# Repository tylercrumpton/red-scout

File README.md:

# Red Scout
## Multi-Purpose Wireless Sensor and Controller Board
Red Scout is a wireless module designed to allow easy collection of data from a variety of sensors, as well providing the ability to control devices like LEDs, relays, motors, and more. It's based on the Synapse SM200 SNAP module, a microcontroller with built-in 802.15.4 wireless meshing that runs Python scripts.

### Overall Features
- Simple wireless communication
- Runs SNAPpy Python scripts
- Open Hardware (CC-BY-SA 4.0)
- Board is customizable for many purposes at assembly time
- Small (less than 10x10cm)
- Uses snap fasteners for connecting sensors and devices

### Assembly-time Configuration
To configure the IO pads of the Red Scout at assembly time, a resistor or jumper can be added to the PD or PU resistor pads for that IO. A resistor soldered to the PD pads is placed between the IO pad and GND, whereas a resistor soldered to the PU pads is placed between the IO pad and VCC. By soldering a zero ohm resistor on PD or PU, the IO pad can be used as VCC or GND instead of its IO function. Example hardware configurations will be added to the documentation in the future.

### AA-Version Features

- Powered by two AA batteries
  - Can last up to year in low power mode
- Two LEDs controlled by PWM pins
- 8 GPIO
  - Each GPIO can be configured to have a pullup or pulldown
  - SPI pins (MISO, MOSI, CLK)
  - I2C pins (SCL, SDA, CLK)
  - UART pins (TX, RX)
  - PWM pin
  - 4 analog inputs
- 3mm mounting holes

### Pinouts

To simplify programming, pin equivalence is given in the table below.

| SM200 pin | Pin Name | RedScout | SNAPpy IO |
|-----------|----------|----------|-----------|
| D3        | PWM7     | P1       |         7 |
| B7        | SCL      | P2       |        31 |
| A7        | SDA      | P3       |        30 |
| B4        | MOSI     | P4       |        25 |
| B1        | MISO     | P5       |        18 |
| A5        | CLK      | P6       |        26 |
| C2        | TX0      | P7       |        17 |
| C1        | RX0      | P8       |        16 |
| D2        | PWM6     | D2       |         6 |
| D1        | PWM5     | D1       |         5 |

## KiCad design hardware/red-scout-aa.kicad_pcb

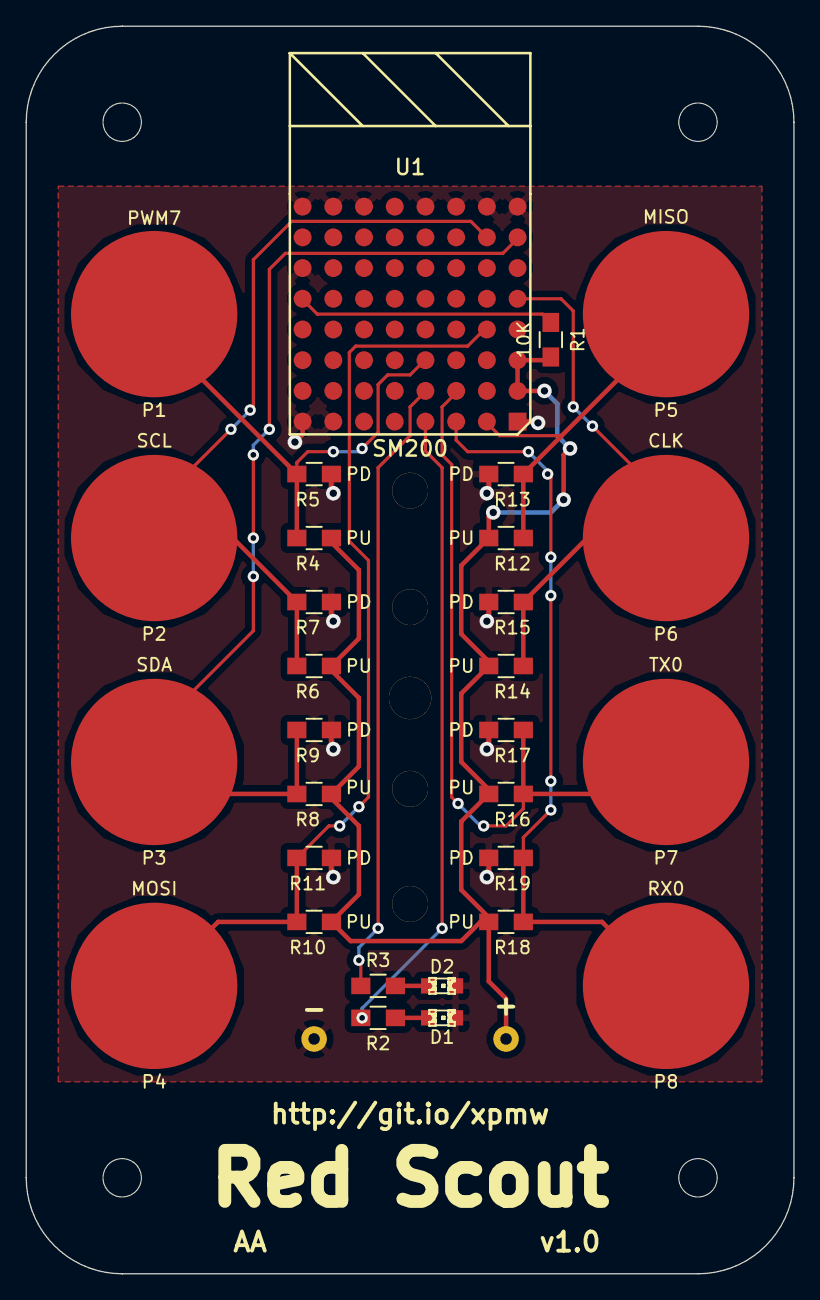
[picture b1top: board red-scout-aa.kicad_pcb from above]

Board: 2 copper layers, 60.0 x 97.5 mm, 35 parts (1 on the bottom side), 15 nets.

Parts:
BT1: BATTERY; AA_battery_holder_12BH321P-GR
D1, D2: LED; LED-0805
MountingHole_3mm, MountingHole_3mm#2, MountingHole_3mm#3, MountingHole_3mm#4: VAL**; MountingHole_3mm
P1: PWM7; 16_snap
P2: SCL; 16_snap
P3: SDA; 16_snap
P4: MOSI; 16_snap
P5: MISO; 16_snap
P6: CLK; 16_snap
P7: TX0; 16_snap
P8: RX0; 16_snap
R1: 10K; R_0805_HandSoldering
R2, R3: 1K; R_0805_HandSoldering
R4, R6, R8, R10, R12, R14, R16, R18: PU; R_0805_HandSoldering
R5, R7, R9, R11, R13, R15, R17, R19: PD; R_0805_HandSoldering
U1: SM200

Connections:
GND: BT1.2, D1.2, D2.2, R5.2, R7.2, R9.2, R11.2, R13.2, R15.2, R17.2, R19.2, U1.A1, U1.A8, U1.B8, U1.C8, U1.D8, U1.F8, U1.G1, U1.G8, U1.H1, U1.H6, U1.H8
MISO: P5.1, R12.1, R13.1, U1.B1
MOSI: P4.1, R10.1, R11.1, U1.B4
unnamed: D1.1, R2.2
unnamed: D2.1, R3.2
unnamed: R1.1, U1.H5
PWM5: R2.1, U1.D1
PWM6: R3.1, U1.D2
PWM7: P1.1, R4.1, R5.1, U1.D3
RX0: P8.1, R18.1, R19.1, U1.C1
SCL: P2.1, R6.1, R7.1, U1.B7
SDA: P3.1, R8.1, R9.1, U1.A7
SPICLK: P6.1, R14.1, R15.1, U1.A5
TX0: P7.1, R16.1, R17.1, U1.C2
VCC: BT1.1, R1.2, R4.2, R6.2, R8.2, R10.2, R12.2, R14.2, R16.2, R18.2, U1.A2, U1.A3

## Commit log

2015-03-05 Started schematic for AA-powered red-scout board.
2015-03-05 Added snap connectors and LEDs.
2015-03-05 Wired up the snaps and nc'ed the unused pins.
2015-03-05 Placed all parts on PCB.
2015-03-06 Finished placing and routing board.
2015-03-06 Finished up the silkscreen.
2015-03-07 Fixed some sharing issues by using submodules.
2015-03-08 Changed submodule link to https instead of ssh.
2015-03-09 Added README.md file.
2015-03-09 Actually added the content to the README this time.
2015-03-09 Added AA-version board image to README.
2015-03-09 Added analog inputs to README.
2015-03-10 Added Assembly-time Configuration documentation.
2015-06-27 Add IO pin headers to schematic.
2015-06-27 Add power switch to schematic.
2015-06-27 Add power switch bypass to schematic.
2015-06-28 Add serial port and fix IO header.
2015-06-28 Label UART1 header.
2015-06-28 Update PCB with UART, GPIO headers, and switch.
2015-08-02 add pin equivalence to the README
